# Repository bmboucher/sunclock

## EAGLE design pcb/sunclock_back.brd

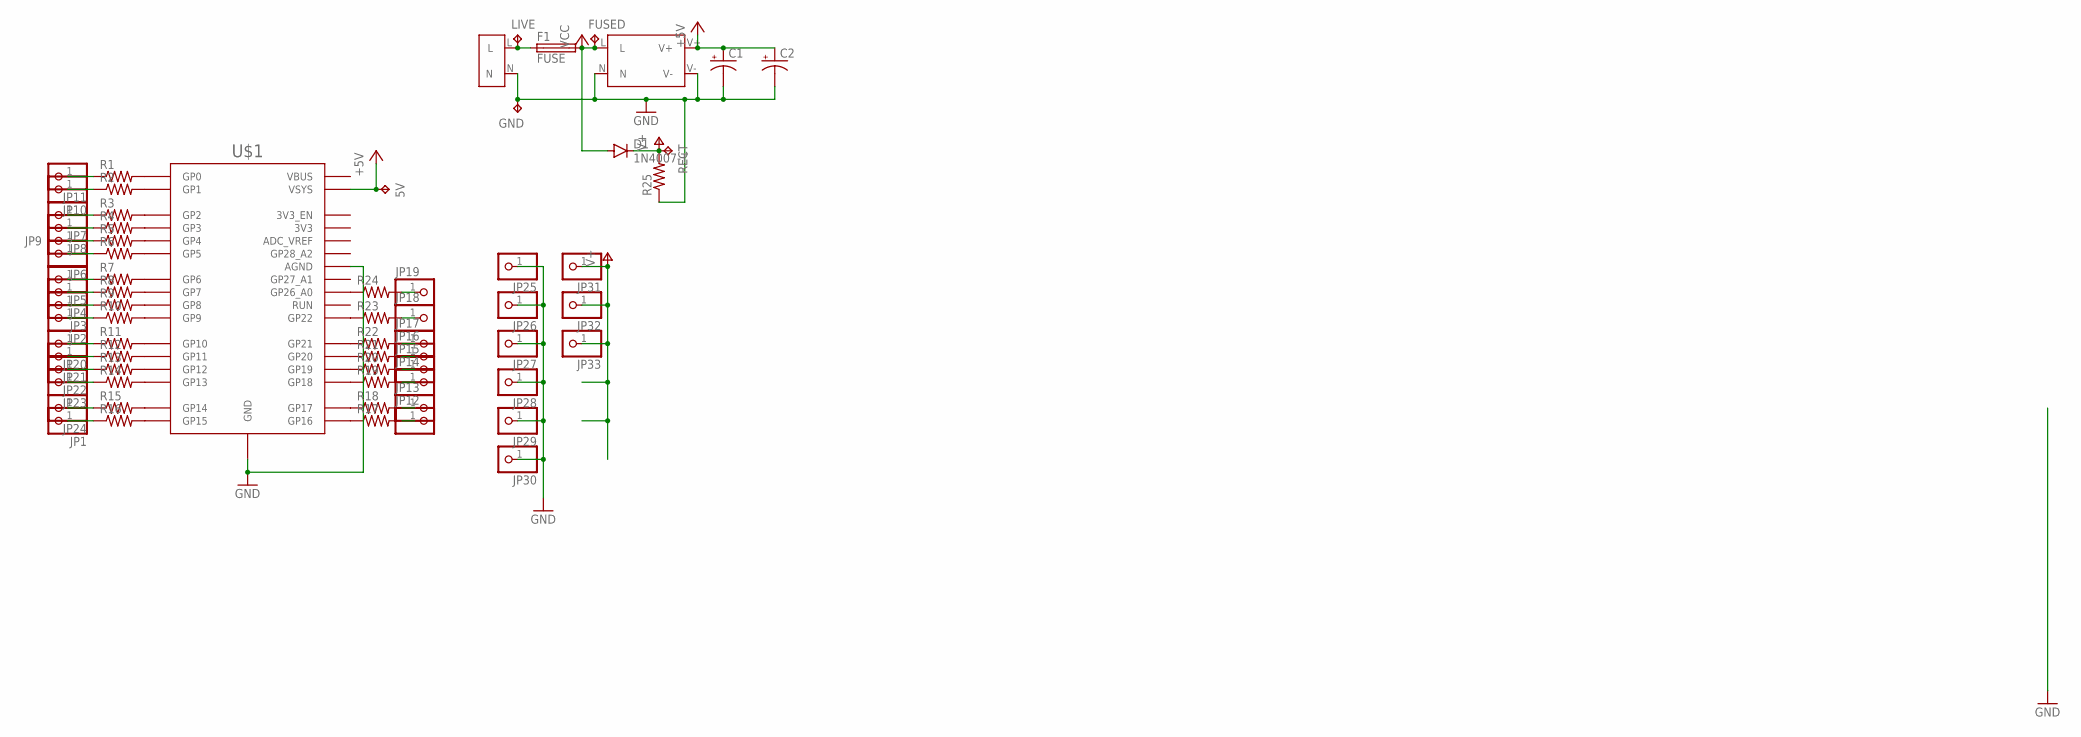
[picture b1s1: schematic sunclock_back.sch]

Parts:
5V: TPB2,54; B2,54
AC1: AC_IN
C1, C2: CPOL-USE3.5-10; E3,5-10
D1: 1N4007-T; DIOAD1140W86L463D236B
F1: FUSE
FUSED: TPB2,54; B2,54
GND: TPB2,54; B2,54
JP1, JP2, JP3, JP4, JP5, JP6, JP7, JP8, JP9, JP10, JP11, JP12, JP13, JP14, JP15, JP16, JP17, JP18, JP19, JP20, JP21, JP22, JP23, JP24, JP25, JP26, JP27, JP28, JP29, JP30, JP31, JP32, JP33: PINHD-1X1; 1X01
LIVE: TPB2,54; B2,54
P1: ACDC
R1, R2, R3, R4, R5, R6, R7, R8, R9, R10, R11, R12, R13, R14, R15, R16, R17, R18, R19, R20, R21, R22, R23, R24, R25: R-US_0204/7; 0204/7
RECT: TPB2,54; B2,54
U$1: RPI_PICO-TH; RPI_PICO_TH

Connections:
+5V: 5V.TP, C1.+, C2.+, P1.V+, U$1.VSYS
GND: AC1.N, C1.-, C2.-, GND.TP, JP25.1, JP26.1, JP27.1, JP28.1, JP29.1, JP30.1, P1.N, P1.V-, R25.1, U$1.AGND, U$1.GND@1 (GND), U$1.GND@2 (GND), U$1.GND@3 (GND), U$1.GND@4 (GND), U$1.GND@6 (GND), U$1.GND@7 (GND), U$1.GND@8 (GND)
unnamed: R1.2, U$1.GP0
unnamed: R2.2, U$1.GP1
unnamed: R3.2, U$1.GP2
unnamed: R4.2, U$1.GP3
unnamed: R5.2, U$1.GP4
unnamed: R6.2, U$1.GP5
unnamed: R7.2, U$1.GP6
unnamed: R8.2, U$1.GP7
unnamed: R9.2, U$1.GP8
unnamed: R10.2, U$1.GP9
unnamed: R11.2, U$1.GP10
unnamed: R12.2, U$1.GP11
unnamed: R13.2, U$1.GP12
unnamed: R14.2, U$1.GP13
unnamed: R15.2, U$1.GP14
unnamed: R16.2, U$1.GP15
unnamed: R17.1, U$1.GP16
unnamed: R18.1, U$1.GP17
unnamed: R19.1, U$1.GP18
unnamed: R20.1, U$1.GP19
unnamed: R21.1, U$1.GP20
unnamed: R22.1, U$1.GP21
unnamed: R23.1, U$1.GP22
unnamed: R24.1, U$1.GP26_A0
unnamed: JP9.1, R5.1
unnamed: JP8.1, R4.1
unnamed: JP7.1, R3.1
unnamed: JP10.1, R2.1
unnamed: JP11.1, R1.1
unnamed: JP6.1, R6.1
unnamed: JP5.1, R7.1
unnamed: JP4.1, R8.1
unnamed: JP3.1, R9.1
unnamed: JP2.1, R10.1
unnamed: JP1.1, R16.1
unnamed: JP20.1, R11.1
unnamed: JP21.1, R12.1
unnamed: JP22.1, R13.1
unnamed: JP23.1, R14.1
unnamed: JP24.1, R15.1
unnamed: JP12.1, R17.2
unnamed: JP13.1, R18.2
unnamed: JP14.1, R19.2
unnamed: JP15.1, R20.2
unnamed: JP16.1, R21.2
unnamed: JP17.1, R22.2
unnamed: JP18.1, R23.2
unnamed: JP19.1, R24.2
unnamed: AC1.L, F1.P$1 (1), LIVE.TP
V+: D1.1 (C), JP31.1, JP32.1, JP33.1, R25.2, RECT.TP
VCC: D1.2 (A), F1.P$2 (2), FUSED.TP, P1.L

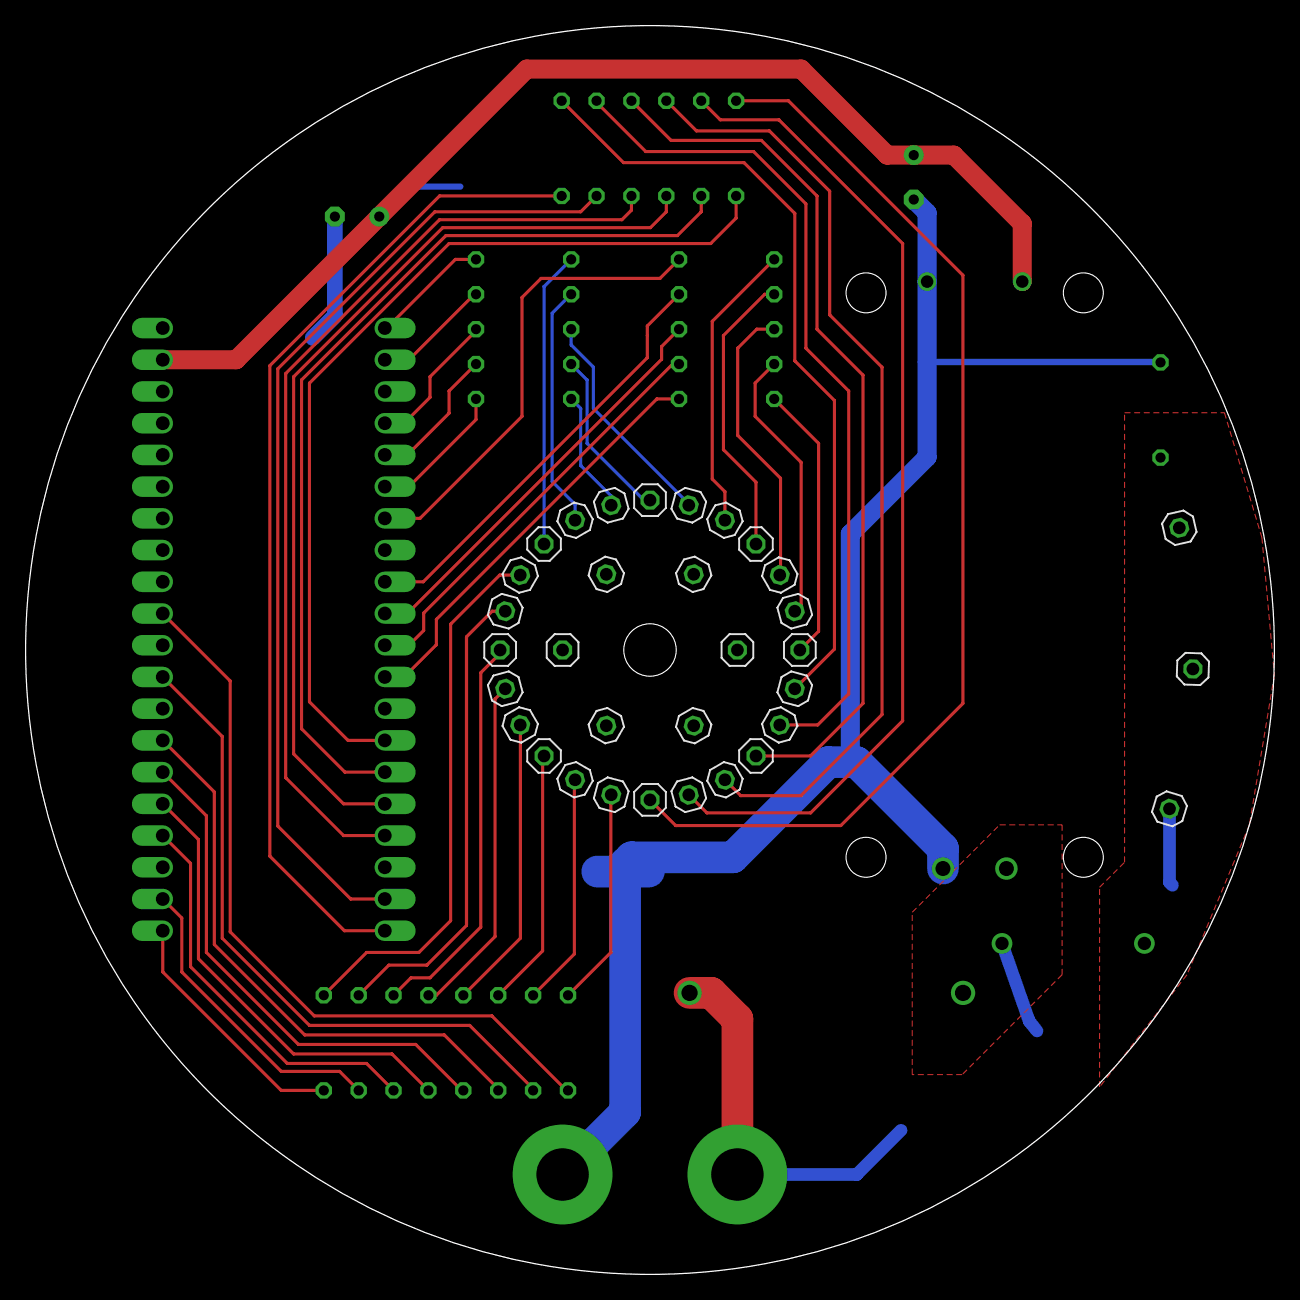
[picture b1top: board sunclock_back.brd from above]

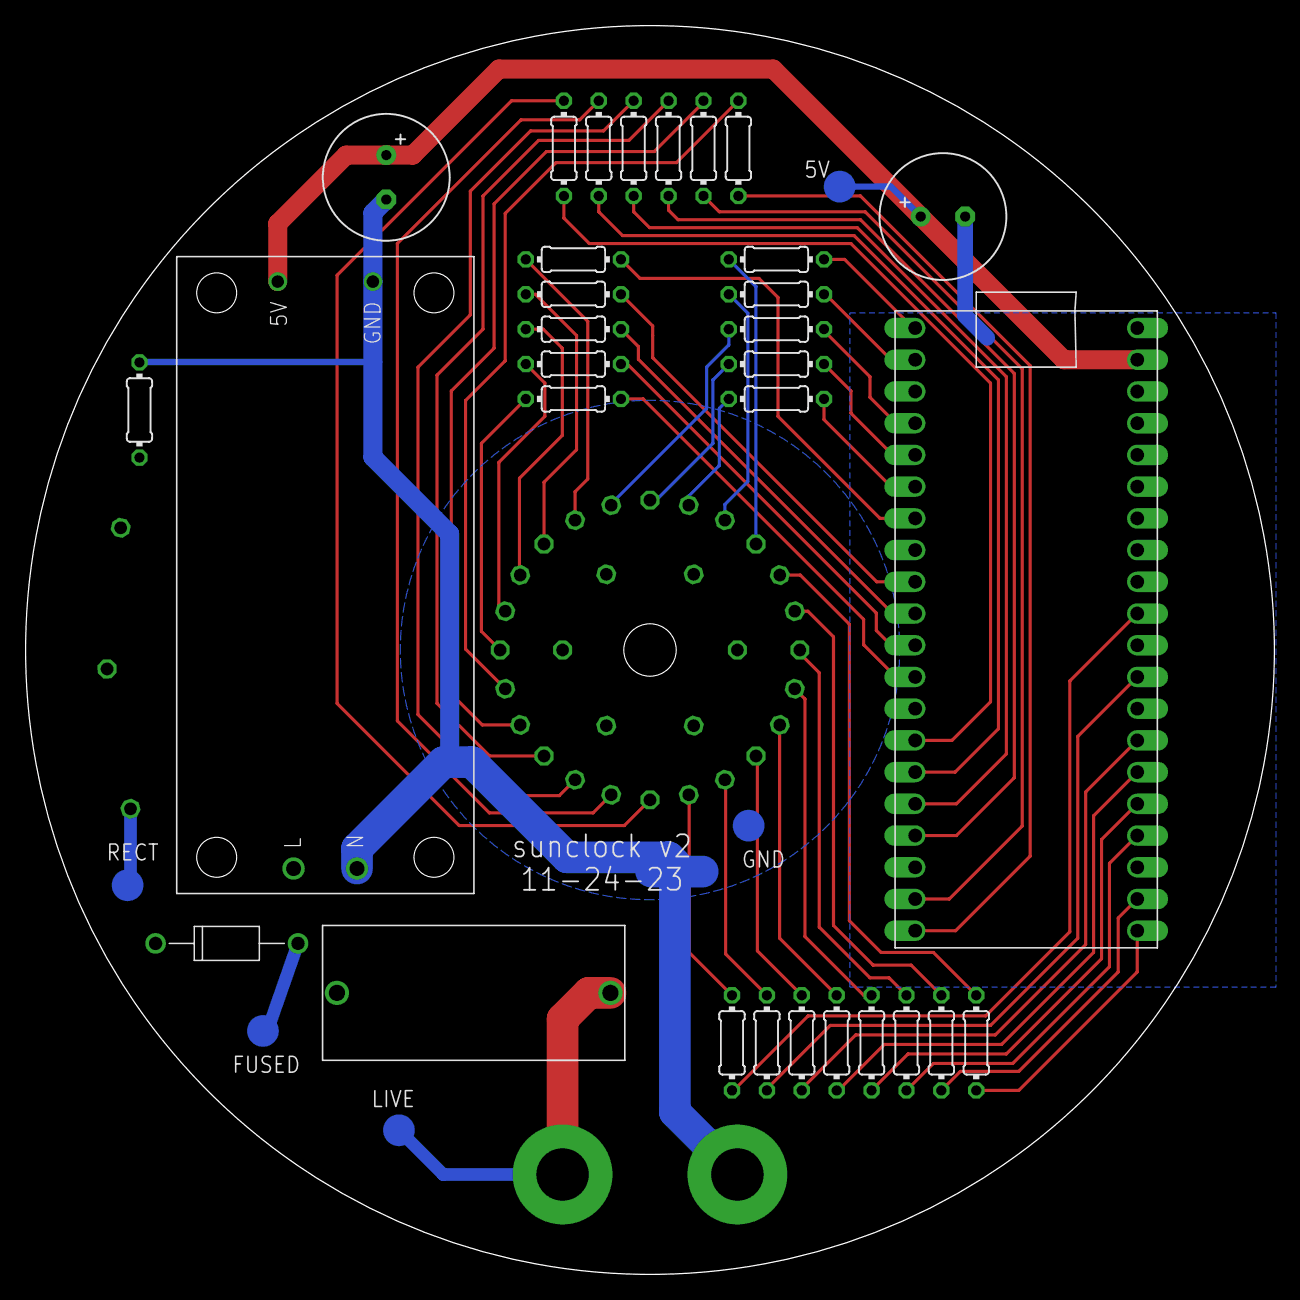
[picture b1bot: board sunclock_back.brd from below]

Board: 2 copper layers, 100.0 x 100.0 mm, 70 parts (36 on the bottom side), 53 nets.

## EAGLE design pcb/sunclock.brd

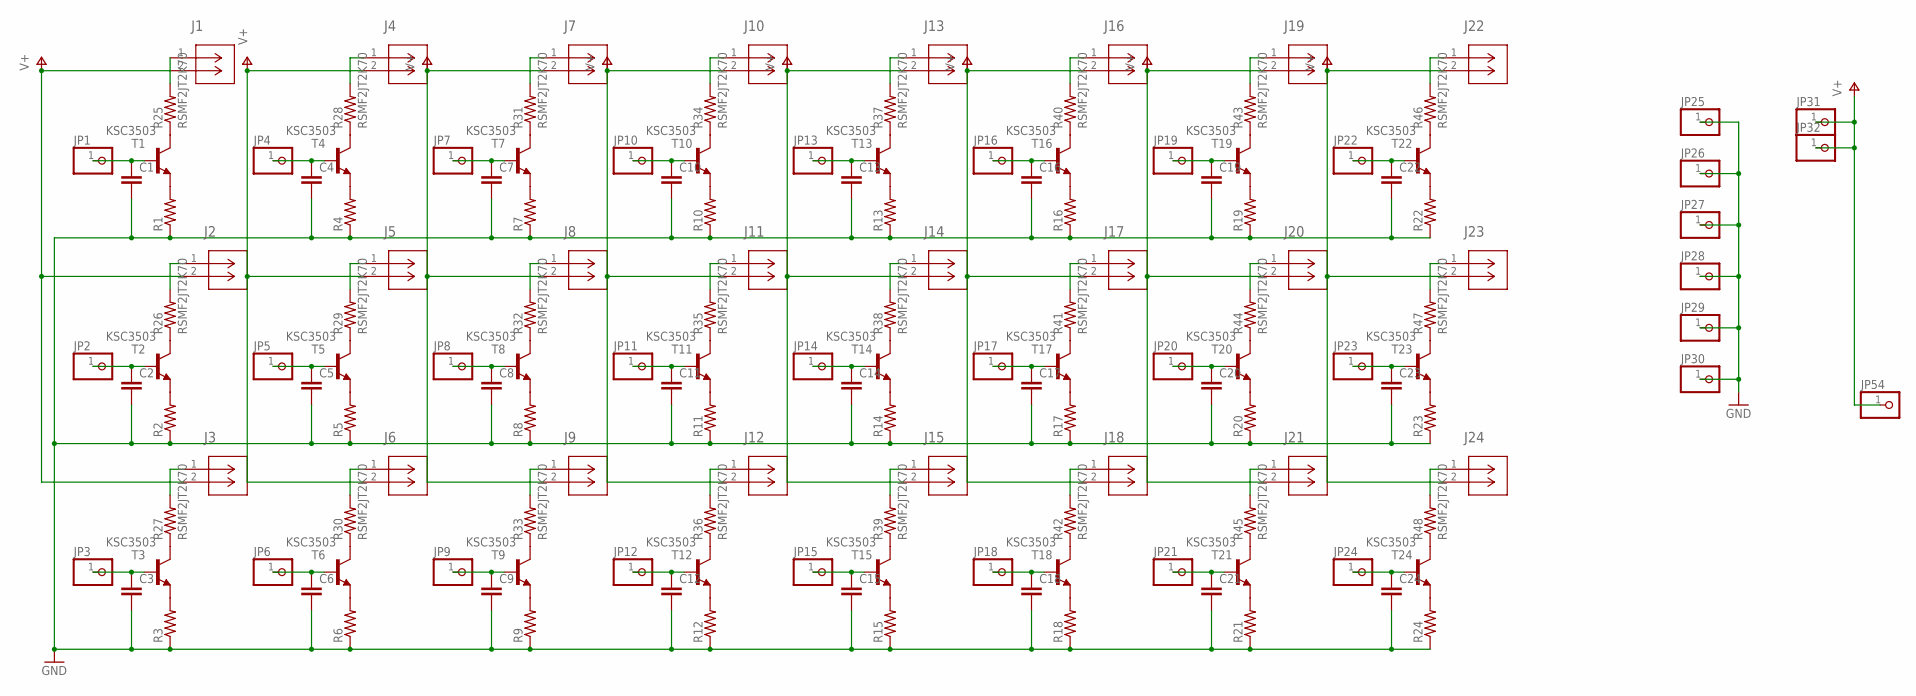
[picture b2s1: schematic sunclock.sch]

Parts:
C1, C2, C3, C4, C5, C6, C7, C8, C9, C10, C11, C12, C13, C14, C15, C16, C17, C18, C19, C20, C21, C22, C23, C24: C-EU050-025X075; C050-025X075
J1, J2, J3, J4, J5, J6, J7, J8, J9, J10, J11, J12, J13, J14, J15, J16, J17, J18, J19, J20, J21, J22, J23, J24: 1776275-2; CONN2_1776275-2
JP1, JP2, JP3, JP4, JP5, JP6, JP7, JP8, JP9, JP10, JP11, JP12, JP13, JP14, JP15, JP16, JP17, JP18, JP19, JP20, JP21, JP22, JP23, JP24, JP25, JP26, JP27, JP28, JP29, JP30, JP31, JP32, JP54: PINHD-1X1; 1X01
R1, R2, R3, R4, R5, R6, R7, R8, R9, R10, R11, R12, R13, R14, R15, R16, R17, R18, R19, R20, R21, R22, R23, R24: R-US_0207/10; 0207/10
R25, R26, R27, R28, R29, R30, R31, R32, R33, R34, R35, R36, R37, R38, R39, R40, R41, R42, R43, R44, R45, R46, R47, R48: RSMF2JT2K70; RESAD1610W80L1100D450B
T1, T2, T3, T4, T5, T6, T7, T8, T9, T10, T11, T12, T13, T14, T15, T16, T17, T18, T19, T20, T21, T22, T23, T24: KSC3503; TO126V_

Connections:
GND: C1.2, C2.2, C3.2, C4.2, C5.2, C6.2, C7.2, C8.2, C9.2, C10.2, C11.2, C12.2, C13.2, C14.2, C15.2, C16.2, C17.2, C18.2, C19.2, C20.2, C21.2, C22.2, C23.2, C24.2, JP25.1, JP26.1, JP27.1, JP28.1, JP29.1, JP30.1, R1.1, R2.1, R3.1, R4.1, R5.1, R6.1, R7.1, R8.1, R9.1, R10.1, R11.1, R12.1, R13.1, R14.1, R15.1, R16.1, R17.1, R18.1, R19.1, R20.1, R21.1, R22.1, R23.1, R24.1
unnamed: C1.1, JP1.1, T1.3 (B)
unnamed: R1.2, T1.1 (E)
unnamed: R25.1, T1.2 (C)
unnamed: J1.1, R25.2
unnamed: R2.2, T2.1 (E)
unnamed: C2.1, JP2.1, T2.3 (B)
unnamed: R26.1, T2.2 (C)
unnamed: J2.1, R26.2
unnamed: C3.1, JP3.1, T3.3 (B)
unnamed: R3.2, T3.1 (E)
unnamed: R27.1, T3.2 (C)
unnamed: J3.1, R27.2
unnamed: J4.1, R28.2
unnamed: J5.1, R29.2
unnamed: J6.1, R30.2
unnamed: R28.1, T4.2 (C)
unnamed: R29.1, T5.2 (C)
unnamed: R30.1, T6.2 (C)
unnamed: R4.2, T4.1 (E)
unnamed: R5.2, T5.1 (E)
unnamed: R6.2, T6.1 (E)
unnamed: C5.1, JP5.1, T5.3 (B)
unnamed: C4.1, JP4.1, T4.3 (B)
unnamed: C6.1, JP6.1, T6.3 (B)
unnamed: R7.2, T7.1 (E)
unnamed: R8.2, T8.1 (E)
unnamed: R9.2, T9.1 (E)
unnamed: R31.1, T7.2 (C)
unnamed: R32.1, T8.2 (C)
unnamed: R33.1, T9.2 (C)
unnamed: J9.1, R33.2
unnamed: J8.1, R32.2
unnamed: J7.1, R31.2
unnamed: C7.1, JP7.1, T7.3 (B)
unnamed: R10.2, T10.1 (E)
unnamed: C8.1, JP8.1, T8.3 (B)
unnamed: R11.2, T11.1 (E)
unnamed: C9.1, JP9.1, T9.3 (B)
unnamed: R12.2, T12.1 (E)
unnamed: R34.1, T10.2 (C)
unnamed: R35.1, T11.2 (C)
unnamed: R36.1, T12.2 (C)
unnamed: J10.1, R34.2
unnamed: J11.1, R35.2
unnamed: J12.1, R36.2
unnamed: C10.1, JP10.1, T10.3 (B)
unnamed: C11.1, JP11.1, T11.3 (B)
unnamed: C12.1, JP12.1, T12.3 (B)
unnamed: R13.2, T13.1 (E)
unnamed: R14.2, T14.1 (E)
unnamed: R15.2, T15.1 (E)
unnamed: R37.1, T13.2 (C)
unnamed: R38.1, T14.2 (C)
unnamed: R39.1, T15.2 (C)
unnamed: J15.1, R39.2
unnamed: J14.1, R38.2
unnamed: J13.1, R37.2
unnamed: C13.1, JP13.1, T13.3 (B)
unnamed: C14.1, JP14.1, T14.3 (B)
unnamed: C15.1, JP15.1, T15.3 (B)
unnamed: R16.2, T16.1 (E)
unnamed: R17.2, T17.1 (E)
unnamed: R18.2, T18.1 (E)
unnamed: R40.1, T16.2 (C)
unnamed: R41.1, T17.2 (C)
unnamed: R42.1, T18.2 (C)
unnamed: J16.1, R40.2
unnamed: J17.1, R41.2
unnamed: J18.1, R42.2
unnamed: C16.1, JP16.1, T16.3 (B)
unnamed: C17.1, JP17.1, T17.3 (B)
unnamed: C18.1, JP18.1, T18.3 (B)
unnamed: R19.2, T19.1 (E)
unnamed: R20.2, T20.1 (E)
unnamed: R21.2, T21.1 (E)
unnamed: R43.1, T19.2 (C)
unnamed: R44.1, T20.2 (C)
unnamed: R45.1, T21.2 (C)
unnamed: J21.1, R45.2
unnamed: J20.1, R44.2
unnamed: J19.1, R43.2
unnamed: C19.1, JP19.1, T19.3 (B)
unnamed: C20.1, JP20.1, T20.3 (B)
unnamed: C21.1, JP21.1, T21.3 (B)
unnamed: R22.2, T22.1 (E)
unnamed: R23.2, T23.1 (E)
unnamed: R24.2, T24.1 (E)
unnamed: R46.1, T22.2 (C)
unnamed: R47.1, T23.2 (C)
unnamed: R48.1, T24.2 (C)
unnamed: J22.1, R46.2
unnamed: J23.1, R47.2
unnamed: J24.1, R48.2
unnamed: C24.1, JP24.1, T24.3 (B)
unnamed: C23.1, JP23.1, T23.3 (B)
unnamed: C22.1, JP22.1, T22.3 (B)
V+: J1.2, J2.2, J3.2, J4.2, J5.2, J6.2, J7.2, J8.2, J9.2, J10.2, J11.2, J12.2, J13.2, J14.2, J15.2, J16.2, J17.2, J18.2, J19.2, J20.2, J21.2, J22.2, J23.2, J24.2, JP31.1, JP32.1, JP54.1

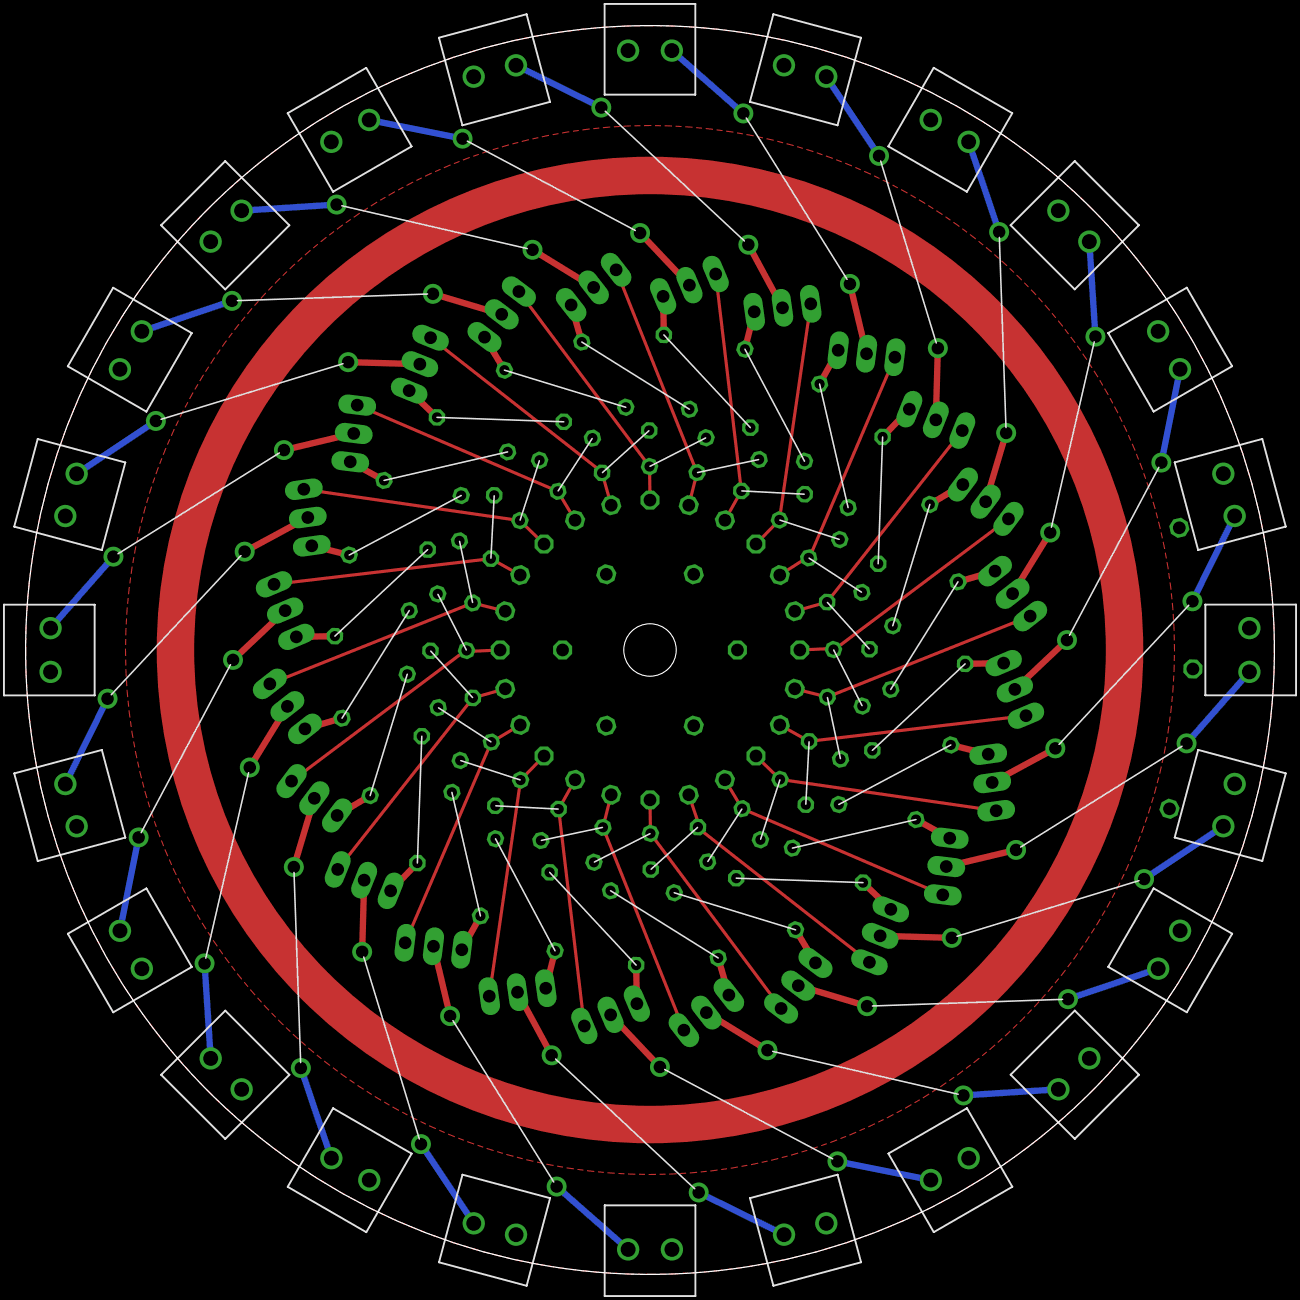
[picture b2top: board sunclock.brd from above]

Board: 2 copper layers, 100.0 x 100.0 mm, 153 parts (0 on the bottom side), 98 nets.

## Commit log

2023-11-26 Adding license
2023-11-26 Changing license to full text
2023-11-26 Removing license

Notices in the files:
parts and their libraries:
COPYRIGHT: Copyright (C) 2023 Ultra Librarian. All rights reserved.
